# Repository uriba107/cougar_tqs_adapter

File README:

== TM cougar TQS USB adapter ==
This is a DIY USB adapter to make your TM Cougar throttle work as a standalone USB device.

This software is distributed under BSD license, and is provided as is and without any warranty what so ever.

http://pits.108vfs.org

==== Other useful stuff ====
===== Hardware =====
My version is based on Atmel ATMEGA 32u4 chip. 
I've been using a replica of Sparkfun's Arduino Pro-Micro, with other versions YMMV.
Schematics can be found in the "hardware" folder.
for more details on the build process:
http://pits.108vfs.org/uriba/standalone-cougar-tqs-part-i/

===== Software =====
Source code provided can compiled and opened using Atmel Studio 6.2.
for more details check out the relevent blog posts:
http://pits.108vfs.org/uriba/standalone-cougar-tqs-part-ii/
http://pits.108vfs.org/uriba/standalone-cougar-tqs-part-iii/

===== Installation =====
Connect the Arduino Pro-micro to the computer, Drivers may be needed.
press the reset button twice in rapid succession to force device into "bootloader" mode.
Your computer will now Identify a new device, please note this device's COM port.
from the AVRdude folder, run the "upload_code.bat" file. In the window opened, type the device's com port number (eg. if device is on COM12, type "12").
double press the reset button of the arduino to force it into bootloaded mode again, and hit Enter. The code will now be uploaded to device. once completed, the device should register as a new joystick.

====== Debugging ======
In the "TQS_debugging" folder, you will find an Arduino sketch to help you debug the hardware.
it will sample the device in exactly the same way the actual code does, but outputs the data out via the Serial console.
compile using "Arduino Micro" in the Arduino IDE.

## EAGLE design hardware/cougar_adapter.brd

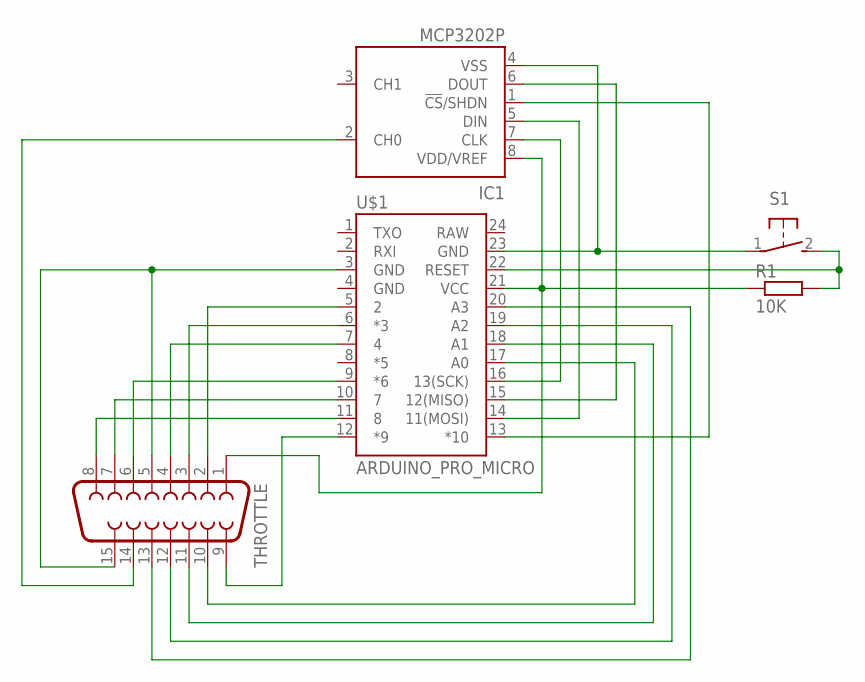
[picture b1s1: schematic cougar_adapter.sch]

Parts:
IC1: MCP3202P; DIL8
R1: 10K; 0204/7
S1: 31-XX; B3F-31XX
THROTTLE: F15HDH; HDF15H
U$1: ARDUINO_PRO_MICRO

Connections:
5V: IC1.8 (VDD/VREF), R1.1, THROTTLE.1, U$1.21 (VCC)
GND: IC1.4 (VSS), S1.1, THROTTLE.5, THROTTLE.15, U$1.3 (GND), U$1.23 (GND)
unnamed: IC1.5 (DIN), U$1.14 (11(MOSI))
unnamed: IC1.6 (DOUT), U$1.15 (12(MISO))
unnamed: IC1.7 (CLK), U$1.16 (13(SCK))
unnamed: R1.2, S1.2 (S), U$1.22 (RESET)
unnamed: THROTTLE.8, U$1.11 (8)
unnamed: THROTTLE.7, U$1.10 (7)
unnamed: THROTTLE.6, U$1.9 (*6)
unnamed: THROTTLE.4, U$1.7 (4)
unnamed: THROTTLE.3, U$1.6 (*3)
unnamed: IC1.2 (CH0), THROTTLE.14
unnamed: THROTTLE.9, U$1.12 (*9)
unnamed: THROTTLE.2, U$1.5 (2)
unnamed: THROTTLE.10, U$1.17 (A0)
unnamed: THROTTLE.11, U$1.18 (A1)
unnamed: THROTTLE.12, U$1.19 (A2)
unnamed: THROTTLE.13, U$1.20 (A3)
unnamed: IC1.1 (!CS!/SHDN), U$1.13 (*10)

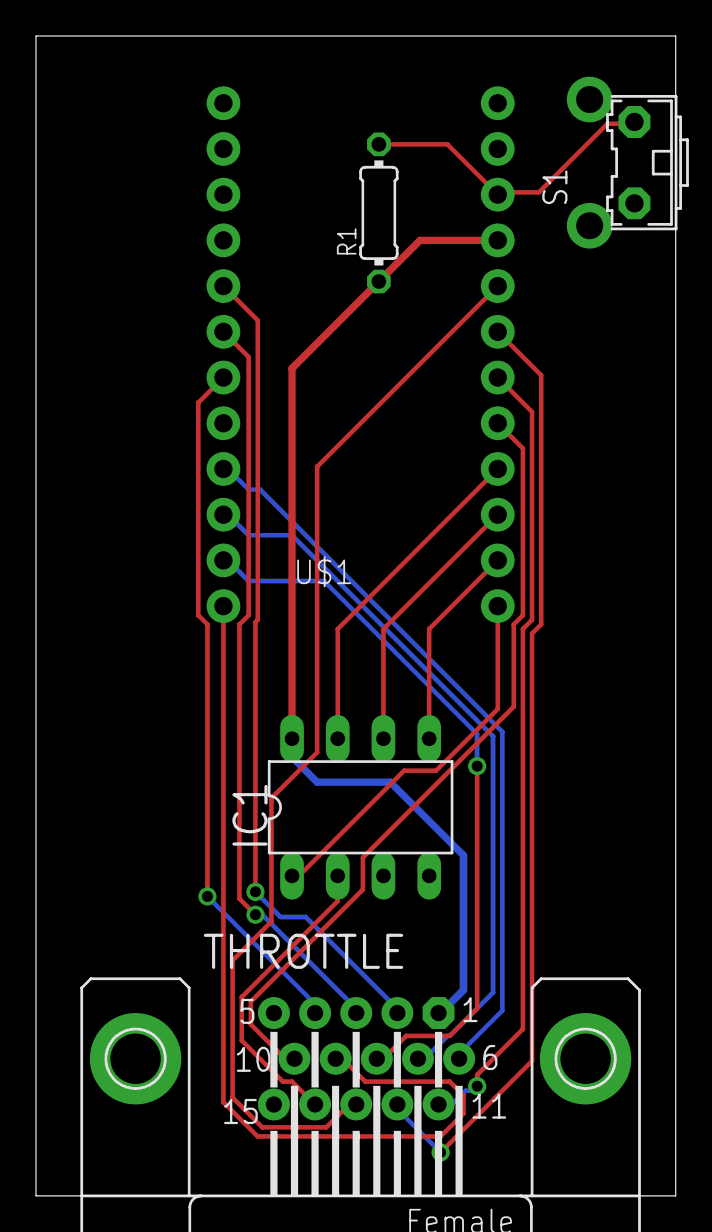
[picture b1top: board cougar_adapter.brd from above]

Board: 2 copper layers, 35.5 x 64.4 mm, 5 parts (0 on the bottom side), 19 nets.

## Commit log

2015-03-17 Initial Commit - working Cougar TQS adapter
2015-03-17 Fix Markdown syntax
2015-03-17 Rename README to README.md
2015-03-17 Update and rename README.txt to README.md
    Switch to proper MD syntax
2015-03-19 Added DEADZONE to microstick (too much for now)
2015-03-19 Version 0.0.2: Better deadzone on the Microstick
2015-08-08 Old cougar and newer cougars might have different pinout on the analog axis. if you move the microstick and roteries value change, use the other option (new/old)
2015-12-23 pre-0.0.3
    Migration to Atmel studio 7.0
    starting implementation of curve on the microstick
2015-12-25 pre-0.0.3 - curves are still in overflow
2015-12-26 0.0.3 - microstick now has a response curve
2015-12-26 0.0.3 - updated FW and documentation
2017-03-23 added license file for the HW
2017-03-24 updated board and schematics
2017-03-25 commits before branching for manu
2017-05-05 TQS adapter rewrite
2017-05-05 Updated README with new User Interface
2017-05-19 Disconnecting Throttle from board will no longer "push all the buttons"
2017-05-19 And now it's actually working
2017-12-16 updated LUFA
2017-12-16 version 0.0.6
2018-01-05 Possible fix for EEPROM loading.
    Adjustments to Microstick and ANT Roteries sensitivities based on Driver feedback
2018-01-06 Update README.md
    Added Link to ViperCore product page
2018-05-29 Attempt to fix eeprom loading. Upgrade LUFA to 170418
2019-09-28 0.0.9 change delay using ADC to allow very long cables to be used. fixed bug in ANT elevation logic.
2019-09-30 fixed microstick
2019-09-30 missing fix
2019-09-30 bumped version to 0.1.0
2019-09-30 fixed curve on ANT
2019-10-04 added cutoff virtual button
2019-10-04 added cutoff virtual button Disabled ANT ELEV curve, it's foobar again.
2019-12-08 bug fixes
2020-04-09 Changed config mode to SbOpen+CursorEnable
2021-10-25 add isChanged logic
2021-10-25 add operator== for tqs struct

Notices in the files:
parts and their libraries:
SparkFun-Boards: Licensing: Creative Commons ShareAlike 4.0 International - https://creativecommons.org/licenses/by-sa/4.0
